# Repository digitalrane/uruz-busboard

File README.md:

Uruz Bus Board for Eurorack
===========================

An OSHW bus board for Eurorack power connectors.
The +5V regulator is optional, and only needed if you don't supply +5V to the input of the bus board.
Includes power LEDs for each voltage rail. Can be daisy-chained with multiple boards using the additional pass connector.

Warranty
========

This bus board will destroy everything you plug into it, remove bookmarks from the books you are reading, and spoil any nearby milk.
Do not use it, and especially don't blame me if something bad happens.

Render
=======

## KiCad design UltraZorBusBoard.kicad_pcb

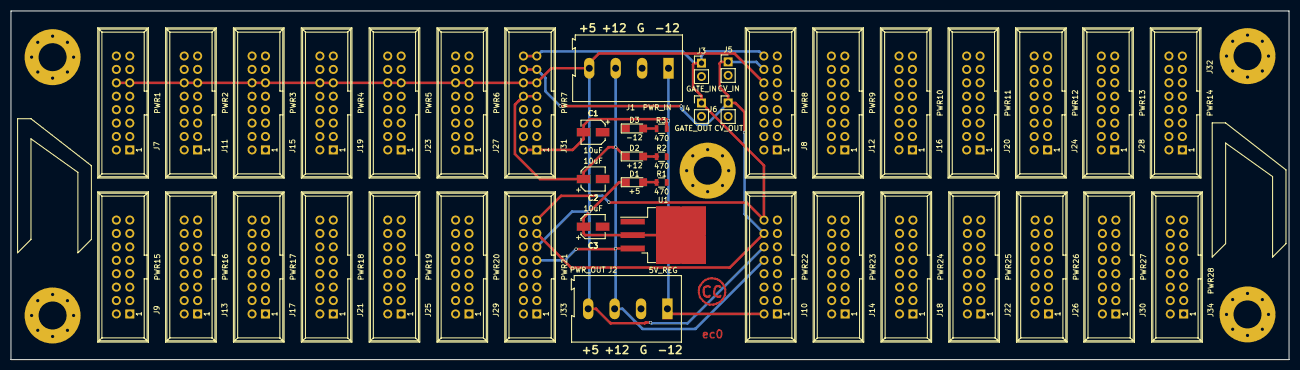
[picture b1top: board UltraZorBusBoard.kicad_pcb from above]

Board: 2 copper layers, 242.0 x 66.0 mm, 44 parts (0 on the bottom side), 9 nets.

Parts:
C1, C2, C3: 10uF; CP_Elec_4x4.5
D1: +5; LED_1206
D2: +12; LED_1206
D3: -12; LED_1206
J1: PWR_IN; AK300-4
J2: PWR_OUT; AK300-4
J3: GATE_IN; Pin_Header_Straight_1x02_Pitch2.54mm
J4: GATE_OUT; Pin_Header_Straight_1x02_Pitch2.54mm
J5: CV_IN; Pin_Header_Straight_1x02_Pitch2.54mm
J6: CV_OUT; Pin_Header_Straight_1x02_Pitch2.54mm
J7: PWR1; IDC_Header_Straight_16pins_silks
J8: PWR8; IDC_Header_Straight_16pins_silks
J9: PWR15; IDC_Header_Straight_16pins_silks
J10: PWR22; IDC_Header_Straight_16pins_silks
J11: PWR2; IDC_Header_Straight_16pins_silks
J12: PWR9; IDC_Header_Straight_16pins_silks
J13: PWR16; IDC_Header_Straight_16pins_silks
J14: PWR23; IDC_Header_Straight_16pins_silks
J15: PWR3; IDC_Header_Straight_16pins_silks
J16: PWR10; IDC_Header_Straight_16pins_silks
J17: PWR17; IDC_Header_Straight_16pins_silks
J18: PWR24; IDC_Header_Straight_16pins_silks
J19: PWR4; IDC_Header_Straight_16pins_silks
J20: PWR11; IDC_Header_Straight_16pins_silks
J21: PWR18; IDC_Header_Straight_16pins_silks
J22: PWR25; IDC_Header_Straight_16pins_silks
J23: PWR5; IDC_Header_Straight_16pins_silks
J24: PWR12; IDC_Header_Straight_16pins_silks
J25: PWR19; IDC_Header_Straight_16pins_silks
J26: PWR26; IDC_Header_Straight_16pins_silks
J27: PWR6; IDC_Header_Straight_16pins_silks
J28: PWR13; IDC_Header_Straight_16pins_silks
J29: PWR20; IDC_Header_Straight_16pins_silks
J30: PWR27; IDC_Header_Straight_16pins_silks
J31: PWR7; IDC_Header_Straight_16pins_silks
J32: PWR14; IDC_Header_Straight_16pins_silks
J33: PWR21; IDC_Header_Straight_16pins_silks
J34: PWR28; IDC_Header_Straight_16pins_silks
R1, R2, R3: 470; R_0805
U1: 5V_REG; TO-263-3_TabPin2

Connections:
+5V: C3.1, D1.1, J1.4, J2.4, J7.11, J7.12, J8.11, J8.12, J9.11, J9.12, J10.11, J10.12, J11.11, J11.12, J12.11, J12.12, J13.11, J13.12, J14.11, J14.12, J15.11, J15.12, J16.11, J16.12, J17.11, J17.12, J18.11, J18.12, J19.11, J19.12, J20.11, J20.12, J21.11, J21.12, J22.11, J22.12, J23.11, J23.12, J24.11, J24.12, J25.11, J25.12, J26.11, J26.12, J27.11, J27.12, J28.11, J28.12, J29.11, J29.12, J30.11, J30.12, J31.11, J31.12, J32.11, J32.12, J33.11, J33.12, J34.11, J34.12, U1.2
+12V: C2.1, D2.1, J1.3, J2.3, J7.9, J7.10, J8.9, J8.10, J9.9, J9.10, J10.9, J10.10, J11.9, J11.10, J12.9, J12.10, J13.9, J13.10, J14.9, J14.10, J15.9, J15.10, J16.9, J16.10, J17.9, J17.10, J18.9, J18.10, J19.9, J19.10, J20.9, J20.10, J21.9, J21.10, J22.9, J22.10, J23.9, J23.10, J24.9, J24.10, J25.9, J25.10, J26.9, J26.10, J27.9, J27.10, J28.9, J28.10, J29.9, J29.10, J30.9, J30.10, J31.9, J31.10, J32.9, J32.10, J33.9, J33.10, J34.9, J34.10, U1.3
-12V: C1.2, J1.1, J2.1, J7.1, J7.2, J8.1, J8.2, J9.2, J10.1, J10.2, J11.1, J11.2, J12.1, J12.2, J14.1, J14.2, J15.1, J15.2, J16.1, J16.2, J18.1, J18.2, J19.1, J19.2, J20.1, J20.2, J22.1, J22.2, J23.1, J23.2, J24.1, J24.2, J26.1, J26.2, J27.1, J27.2, J28.1, J28.2, J30.1, J30.2, J31.1, J31.2, J32.1, J32.2, J34.1, J34.2, R3.1
/CV: J5.1, J6.1, J7.13, J7.14, J8.13, J8.14, J9.13, J9.14, J10.13, J10.14, J11.13, J11.14, J12.13, J12.14, J13.13, J13.14, J14.13, J14.14, J15.13, J15.14, J16.13, J16.14, J17.13, J17.14, J18.13, J18.14, J19.13, J19.14, J20.13, J20.14, J21.13, J21.14, J22.13, J22.14, J23.13, J23.14, J24.13, J24.14, J25.13, J25.14, J26.13, J26.14, J27.13, J27.14, J28.13, J28.14, J29.13, J29.14, J30.13, J30.14, J31.13, J31.14, J32.13, J32.14, J33.13, J33.14, J34.13, J34.14
/GATE: J3.1, J4.1, J7.15, J7.16, J8.15, J8.16, J9.15, J9.16, J10.15, J10.16, J11.15, J11.16, J12.15, J12.16, J13.15, J13.16, J14.15, J14.16, J15.15, J15.16, J16.15, J16.16, J17.15, J17.16, J18.15, J18.16, J19.15, J19.16, J20.15, J20.16, J21.15, J21.16, J22.15, J22.16, J23.15, J23.16, J24.15, J24.16, J25.15, J25.16, J26.15, J26.16, J27.15, J27.16, J28.15, J28.16, J29.15, J29.16, J30.15, J30.16, J31.15, J31.16, J32.15, J32.16, J33.15, J33.16, J34.15, J34.16
GND: C1.1, C2.2, C3.2, D3.1, J1.2, J2.2, J3.2, J4.2, J5.2, J6.2, J7.3, J7.4, J7.5, J7.6, J7.7, J7.8, J8.3, J8.4, J8.5, J8.6, J8.7, J8.8, J9.3, J9.4, J9.5, J9.6, J9.7, J9.8, J10.3, J10.4, J10.5, J10.6, J10.7, J10.8, J11.3, J11.4, J11.5, J11.6, J11.7, J11.8, J12.3, J12.4, J12.5, J12.6, J12.7, J12.8, J13.3, J13.4, J13.5, J13.6, J13.7, J13.8, J14.3, J14.4, J14.5, J14.6, J14.7, J14.8, J15.3, J15.4, J15.5, J15.6, J15.7, J15.8, J16.3, J16.4, J16.5, J16.6, J16.7, J16.8, J17.3, J17.4, J17.5, J17.6, J17.7, J17.8, J18.3, J18.4, J18.5, J18.6, J18.7, J18.8, J19.3, J19.4, J19.5, J19.6, J19.7, J19.8, J20.3, J20.4, J20.5, J20.6, J20.7, J20.8, J21.3, J21.4, J21.5, J21.6, J21.7, J21.8, J22.3, J22.4, J22.5, J22.6, J22.7, J22.8, J23.3, J23.4, J23.5, J23.6, J23.7, J23.8, J24.3, J24.4, J24.5, J24.6, J24.7, J24.8, J25.3, J25.4, J25.5, J25.6, J25.7, J25.8, J26.3, J26.4, J26.5, J26.6, J26.7, J26.8, J27.3, J27.4, J27.5, J27.6, J27.7, J27.8, J28.3, J28.4, J28.5, J28.6, J28.7, J28.8, J29.3, J29.4, J29.5, J29.6, J29.7, J29.8, J30.3, J30.4, J30.5, J30.6, J30.7, J30.8, J31.3, J31.4, J31.5, J31.6, J31.7, J31.8, J32.3, J32.4, J32.5, J32.6, J32.7, J32.8, J33.3, J33.4, J33.5, J33.6, J33.7, J33.8, J34.3, J34.4, J34.5, J34.6, J34.7, J34.8, R1.2, R2.2, U1.1
unnamed: D1.2, R1.1
unnamed: D2.2, R2.1
unnamed: D3.2, R3.2

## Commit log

2020-08-26 Added README
